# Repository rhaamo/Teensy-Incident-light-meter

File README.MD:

Teensy Light Meter
--------

### Links

 * <a href="./CALIBRATION.md">Calibration and notes</a>
 * <a href="./USAGE.md">How to use the firmware</a>
 * See the pics folder for more pictures

### Software

    $ git clone
    $ cd project/LightMeterV2
    $ pio lib install
    $ pio run
    $ pio run --target upload

Notes:
  The TSL25x1 lib I use is either custom, or hacked from anoter one. We setup the sensor and powerup on setup(), then let it run freely.

  The sensor do it's integration time by itself, we NEVER poweroff the sensor, then we read the value as the loop loops.

  This is done to avoid the 120ms*integrationTime etc. delay, the loop is ultra fast, then buttons are reactive.

  And we can then set the sensor to a high integration value without having 500ms delay introduced in the loop.

### Notes

The Light Meter isn't super slim, but not too big, it could get 5mm less easily if the pins connecting the teensyview were trimmed.

Without trimming everything used is stock without modifications. Also the OLED display PCB is way bigger than the LCD itself, and that forbig to reduce by ~3mm without having an ugly PCB popping out. Trimming the pins will be envisaged in the future.

The choosen battery was a BL-5C because I have one spare, but any with a JST connector would do the job, only the middle part and bottom of the enclosure would need redesign. The battery connector is some sort of wire bended, passed through a hole and glued after soldering. Not the best but I didn't wanted to wait a month to get a small 3-pins 3mm pitch battery connector to design the enclosure.

The stock BL-5C, genuine, is a 1000mAh battery, the Light Meter, with sensor free-running is consuming about 40mA according to the battery charger, which allows between 17 and 25 hours of continus running, in theory. You can still easily swap battery anyway, just bring the right screwdriver, and spare charged batteries with you.

The USB data is hard wired between the D+/D- pads of the teensy to the battery babysitter, allowing to program the teensy from the battery charger directly without doing anything, reset button is useless as we are using the stock teensy bootloader, permitting remote flash and reboot.

The TSL2591 doesn't permit changing I2C address, you can only have one.

### Todo

 - Design some sort of sliding window to protect the sensor
 - Games, because why not ?

### Hardware

Uses the following:

* [Teensy 3.2](https://www.sparkfun.com/products/13736)
* [TeensyView](https://www.sparkfun.com/products/14048) (ALTERNATE mode)
* [TSL2591 HDR Light Sensor](https://www.adafruit.com/product/1980)
* [Battery Babysitter](https://www.sparkfun.com/products/13777)
* [Rotary Encoder with Red/Green led](https://www.digikey.fr/product-detail/fr/bourns-inc/PEL12D-4225S-S2024/PEL12D-4225S-S2024-ND/2498880)
* [Knob, transparent](https://www.digikey.fr/product-detail/fr/sparkfun-electronics/COM-10597/1568-1838-ND/7229845)
* Battery: BL-5C (1000mAh nokia battery)
* Mini switch: 6mm push button
* Diode: 1N4148
* Transistor: 2N3940, TO-92
* Resistor: 4.7k
* Capacitor: 10uF, radial, polarised
* A PCB from the PCB folder

Some build notes :
 - The battery can be either connected from the JST connector (DIY enclosure) or from the pads right next to it (provided enclosure)
 - The D+ and D- from USB should be soldered on the teensy first before soldering it to the PCB, make sure to mark with a marker the D- wire. Then after soldering the teensy and the babysitter, twist the two DATA wires and solder them accordingly to the babysitter very small pads.
 - The TSL2591 use four wire (Vcc, GND, SDA, SCL) and ideally use two small connectors, allowing for quick disconnect, for either hacking or easy replacement.
 - The TeensyView needs to be in ALTERNATE mode, cut some jumper pads and solder the others before sticking the OLED glass. Look at Sparkfun docs for that part.
 - The Alternate mode is unfortunately needed because of the pins 10 & 11 which are already used for the RED and Green LEDs. A next revision can change that.
 - The TeensyView pins are connected by using standard "long" headers, see ```pics/main_pcb_battery_babysitter.jpg``` for soldering. Also you will have to trim the headers by 5mm on top, to make the display closed to the teensy.
 - You have to put the battery babysitter switch to the OFF position, or it will override the power-on/off feature.

*Schematic diagram.  Click to enlarge.*

### Enclosure

3D designed, printed, works great, to be published.

### PCB

*An assembly*

 * Use libraries:
  * https://github.com/XenGi/teensy.pretty
  * https://github.com/XenGi/teensy_library
  * RGB Encoder Footprint and Library from https://github.com/sparkfun/Rotary_Encoder_Breakout-Illuminated

### License

Uses code from:
  * https://github.com/marshalltaylorSFE/Teensy-Incident-light-meter
  * https://github.com/kevinagnes/diycolorlightmeter/

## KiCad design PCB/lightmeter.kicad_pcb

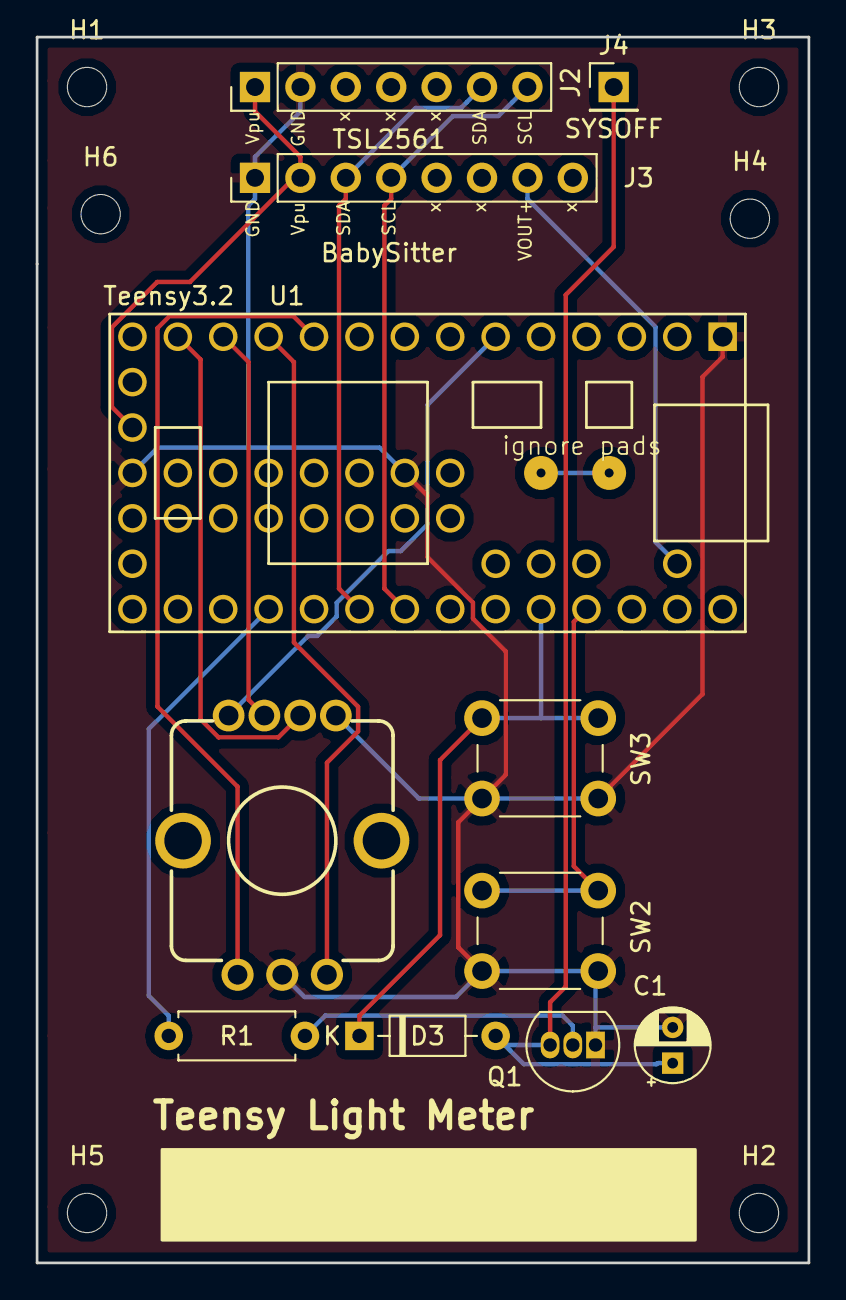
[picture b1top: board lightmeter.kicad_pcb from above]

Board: 2 copper layers, 43.2 x 68.6 mm, 17 parts (0 on the bottom side), 15 nets.

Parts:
C1: 10uF; CP_Radial_D4.0mm_P2.00mm
D3: 1N4148; D_DO-35_SOD27_P7.62mm_Horizontal
H1, H2, H3, H4, H5, H6: MountingHole; MountingHole_2.2mm_M2
J2: TSL2561; PinHeader_1x07_P2.54mm_Vertical
J3: BabySitter; PinHeader_1x08_P2.54mm_Vertical
J4: SYSOFF; PinHeader_1x01_P2.54mm_Vertical
Q1: 2N3904; TO-92_Inline
R1: 4.7k; R_Axial_DIN0207_L6.3mm_D2.5mm_P7.62mm_Horizontal
SW2: DOWN; SW_PUSH_6mm
SW3: UP; SW_PUSH_6mm
U1: Teensy3.2; Teensy30_31_32_LC
U2: ENCODER_2LED; ENCODER_LED_2_KIT

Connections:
/VOUT+: J3.7, U1.34
ENC_A: U1.10, U2.A
ENC_B: U1.11, U2.B
GND: C1.2, J2.2, J3.1, Q1.1, SW2.2, SW3.2, U1.1, U1.17, U1.39, U2.C, U2.GND
LED_G: U1.13, U2.+G
LED_R: U1.12, U2.+R
unnamed: C1.1, D3.2, J4.1, Q1.3
unnamed: D3.1, SW3.1, U1.29
unnamed: Q1.2, R1.1
unnamed: SW2.1, U1.30
PWROFF: R1.2, U1.23
SCL: J2.7, J3.4, U1.26
SDA: J2.6, J3.3, U1.25
SW_ROT: U1.6, U2.SW
Vpu: J2.1, J3.2, U1.16

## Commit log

2019-01-04 Remove unused 3D Bezel
2019-01-04 Switch whole project to PlatformIO
2019-01-04 Code style
2019-01-04 Unused thing
2019-01-04 Clang-format
2019-01-04 Add V2 of the firmware; Full rewrite with others libs for input handling
2019-01-04 Unused now
2019-01-04 More things
2019-01-04 Try to doc
2019-01-05 Really set integration time; Add comments
2019-01-05 Add a few placeholder for new features
2019-01-08 coin
2019-01-08 Fix buttons issue; Use callbacks for the state machine
2019-01-08 Fix trigger state not working
2019-01-08 Remove older firmware
2019-01-08 Add PCB
2019-01-10 Somewhat fix encoder issue
2019-01-10 Fix drawing for f10.x, move left bracket 5px on the right
2019-01-10 Fix get lux display; Add d0 d1 label
2019-01-13 Add no-delay timer for LEDs
2019-01-13 Try to implement blinker duration
2019-01-13 Implement led statuses
2019-01-13 Add led ko when shutdown fails
2019-01-15 Add pics
2019-01-15 Switching to TSL2691; Adafruit lib; And another code; Also remove accumulator thing
2019-01-15 Fix lib name
2019-01-15 Add custom boot logo
2019-01-15 Remove debug messages
2019-01-15 Add adafruit source inplace
2019-01-15 Add hacky Adafruit inplace; Add more fps for cine
2019-01-16 Best value I can find right now
2019-01-16 Add libreoffice calc I used to get the best K-value
2019-01-16 Improved a bit the lux thingy; High/low gain with slow/fast integration time; Added more things to the debug line
2019-01-16 Add some calibration notes
2019-01-16 Add USAGE doc
2019-01-16 make it bigger
2019-01-16 Specify calibration is only valid for reflected
2019-01-16 add a bunch of pics
2019-01-16 Add some more docs to the readme
2019-01-16 TeensyView alternate mode
2019-01-16 battery
2019-01-17 Add hold indicator on raw lux page
2019-01-17 Fix ir/visible label
2019-01-17 Moved to readme
2019-01-17 Yes unfortunately
2019-01-17 Implement 1h auto shutdown if no input handling
2019-01-17 Implement correct led blinking
2019-01-17 Remove unused things
2019-01-17 Reformat code
2019-01-17 reformat, lint
2019-01-17 Unused
2019-01-18 Seems fine
2020-09-15 Add v1 proto enclosure
2021-05-15 update KValue to something apparently... better ?
2021-05-17 switch to bh1750 sensor
